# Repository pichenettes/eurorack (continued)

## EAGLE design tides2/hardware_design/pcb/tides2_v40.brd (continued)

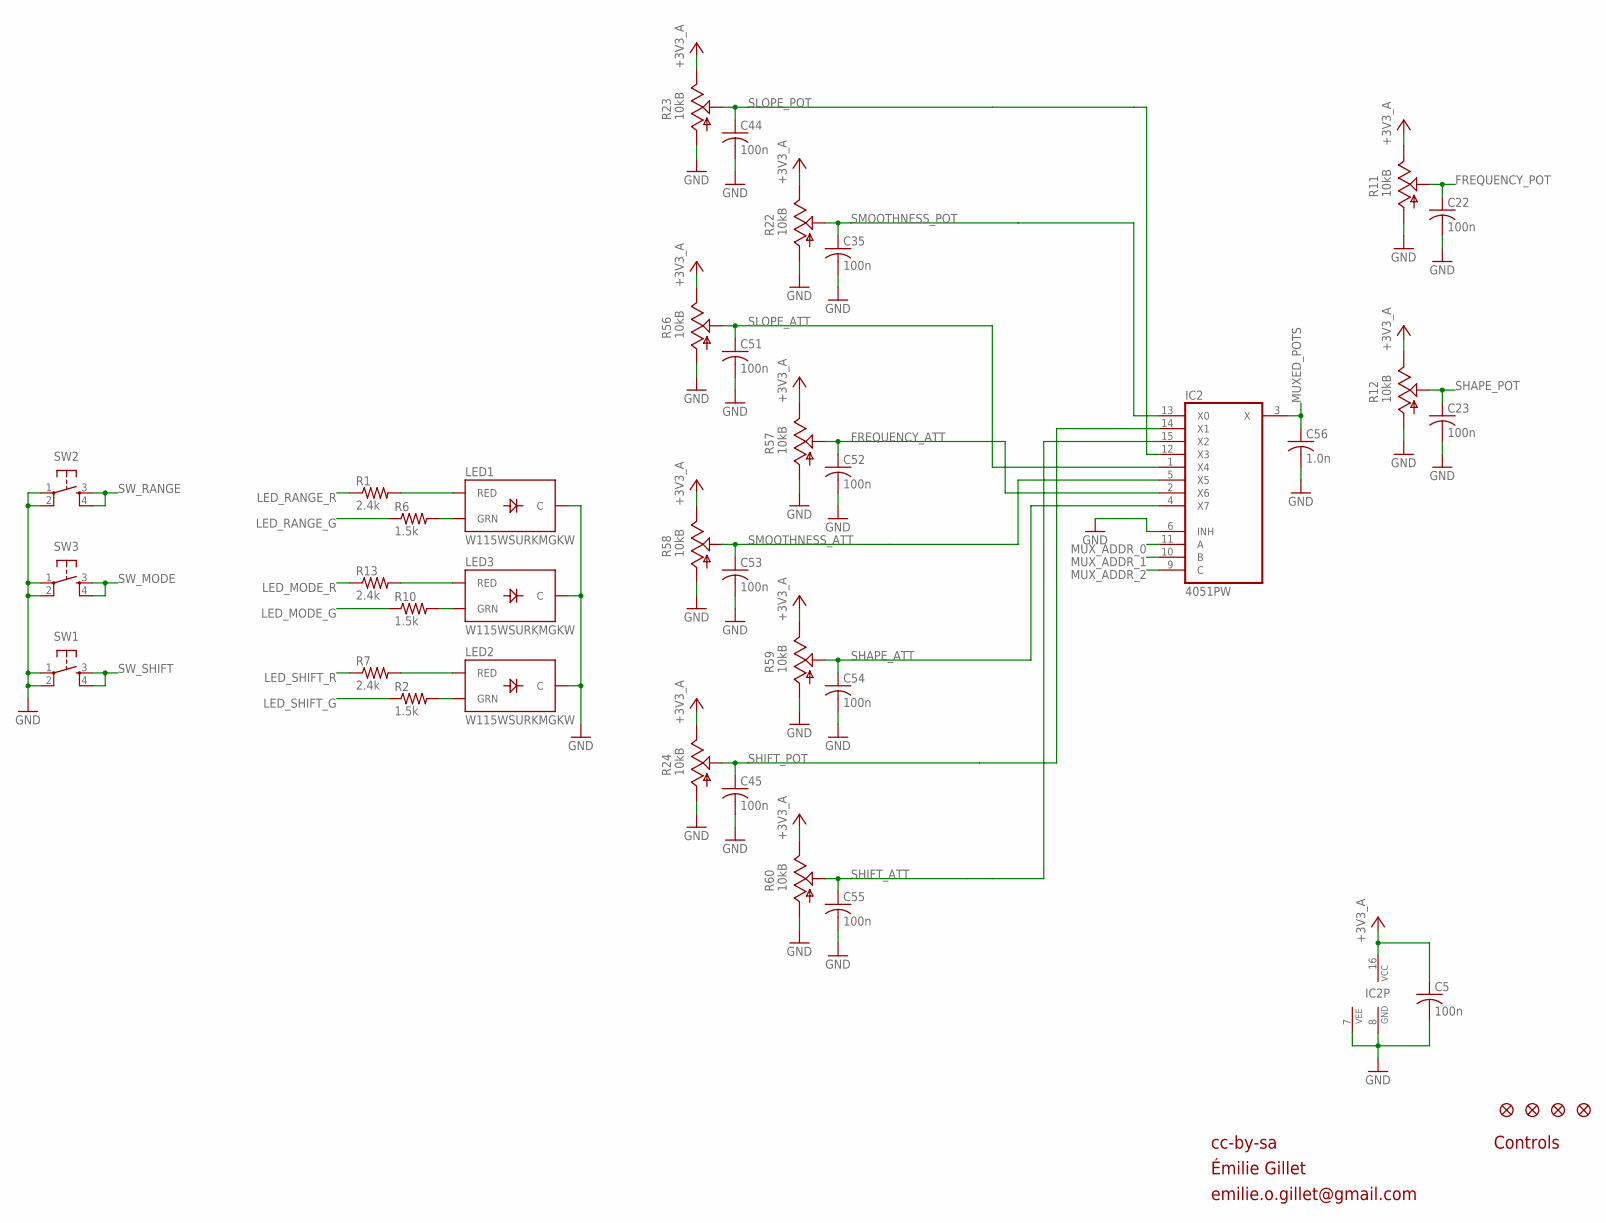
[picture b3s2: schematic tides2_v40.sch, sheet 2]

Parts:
C5, C22, C23, C35, C44, C45, C51, C52, C53, C54, C55: 100n; C0402
C56: 1.0n; C0402
IC2: 4051PW; TSSOP16_065
JP1, JP2, JP3, JP4: FIDUCIAL1X2; FIDUCIAL-1X2
LED1, LED2, LED3: W115WSURKMGKW; LED-BICOLOR-THROUGHHOLE-2.54
R1, R7, R13: 2.4k; R0402
R2, R6, R10: 1.5k; R0402
R11, R12, R22, R23, R24: 10kB; ALPS_POT_VERTICAL_PS
R56, R57, R58, R59, R60: 10kB; ALPS_POT_VERTICAL
SW1, SW2, SW3: TAC_SWITCHPTH; TACTILE-PTH

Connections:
+3V3_A: C5.1, IC2.16 (VCC), R11.P$1 (E), R12.P$1 (E), R22.P$1 (E), R23.P$1 (E), R24.P$1 (E), R56.P$1 (E), R57.P$1 (E), R58.P$1 (E), R59.P$1 (E), R60.P$1 (E); also elsewhere on the board
FREQUENCY_ATT: C52.1, IC2.2 (X6), R57.P$2 (S)
FREQUENCY_POT: C22.1, R11.P$2 (S); also elsewhere on the board
GND: C5.2, C22.2, C23.2, C35.2, C44.2, C45.2, C51.2, C52.2, C53.2, C54.2, C55.2, C56.2, IC2.6 (INH), IC2.7 (VEE), IC2.8 (GND), LED1.2 (C), LED2.2 (C), LED3.2 (C), R11.P$3 (A), R12.P$3 (A), R22.P$3 (A), R23.P$3 (A), R24.P$3 (A), R56.P$3 (A), R57.P$3 (A), R58.P$3 (A), R59.P$3 (A), R60.P$3 (A), SW1.1, SW1.2, SW2.1, SW2.2, SW3.1, SW3.2; also elsewhere on the board
LED_MODE_G: R10.1; also elsewhere on the board
LED_MODE_R: R13.1; also elsewhere on the board
LED_RANGE_G: R6.1; also elsewhere on the board
LED_RANGE_R: R1.1; also elsewhere on the board
LED_SHIFT_G: R2.1; also elsewhere on the board
LED_SHIFT_R: R7.1; also elsewhere on the board
MUXED_POTS: C56.1, IC2.3 (X); also elsewhere on the board
MUX_ADDR_0: IC2.11 (A); also elsewhere on the board
MUX_ADDR_1: IC2.10 (B); also elsewhere on the board
MUX_ADDR_2: IC2.9 (C); also elsewhere on the board
unnamed: LED1.3 (RED), R1.2
unnamed: LED3.3 (RED), R13.2
unnamed: LED3.1 (GRN), R10.2
unnamed: LED2.3 (RED), R7.2
unnamed: LED1.1 (GRN), R6.2
unnamed: LED2.1 (GRN), R2.2
SHAPE_ATT: C54.1, IC2.4 (X7), R59.P$2 (S)
SHAPE_POT: C23.1, R12.P$2 (S); also elsewhere on the board
SHIFT_ATT: C55.1, IC2.15 (X2), R60.P$2 (S)
SHIFT_POT: C45.1, IC2.14 (X1), R24.P$2 (S)
SLOPE_ATT: C51.1, IC2.1 (X4), R56.P$2 (S)
SLOPE_POT: C44.1, IC2.12 (X3), R23.P$2 (S)
SMOOTHNESS_ATT: C53.1, IC2.5 (X5), R58.P$2 (S)
SMOOTHNESS_POT: C35.1, IC2.13 (X0), R22.P$2 (S)
SW_MODE: SW3.3, SW3.4; also elsewhere on the board
SW_RANGE: SW2.3, SW2.4; also elsewhere on the board
SW_SHIFT: SW1.3, SW1.4; also elsewhere on the board

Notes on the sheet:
cc-by-sa
Controls
Émilie Gillet
emilie.o.gillet@gmail.com

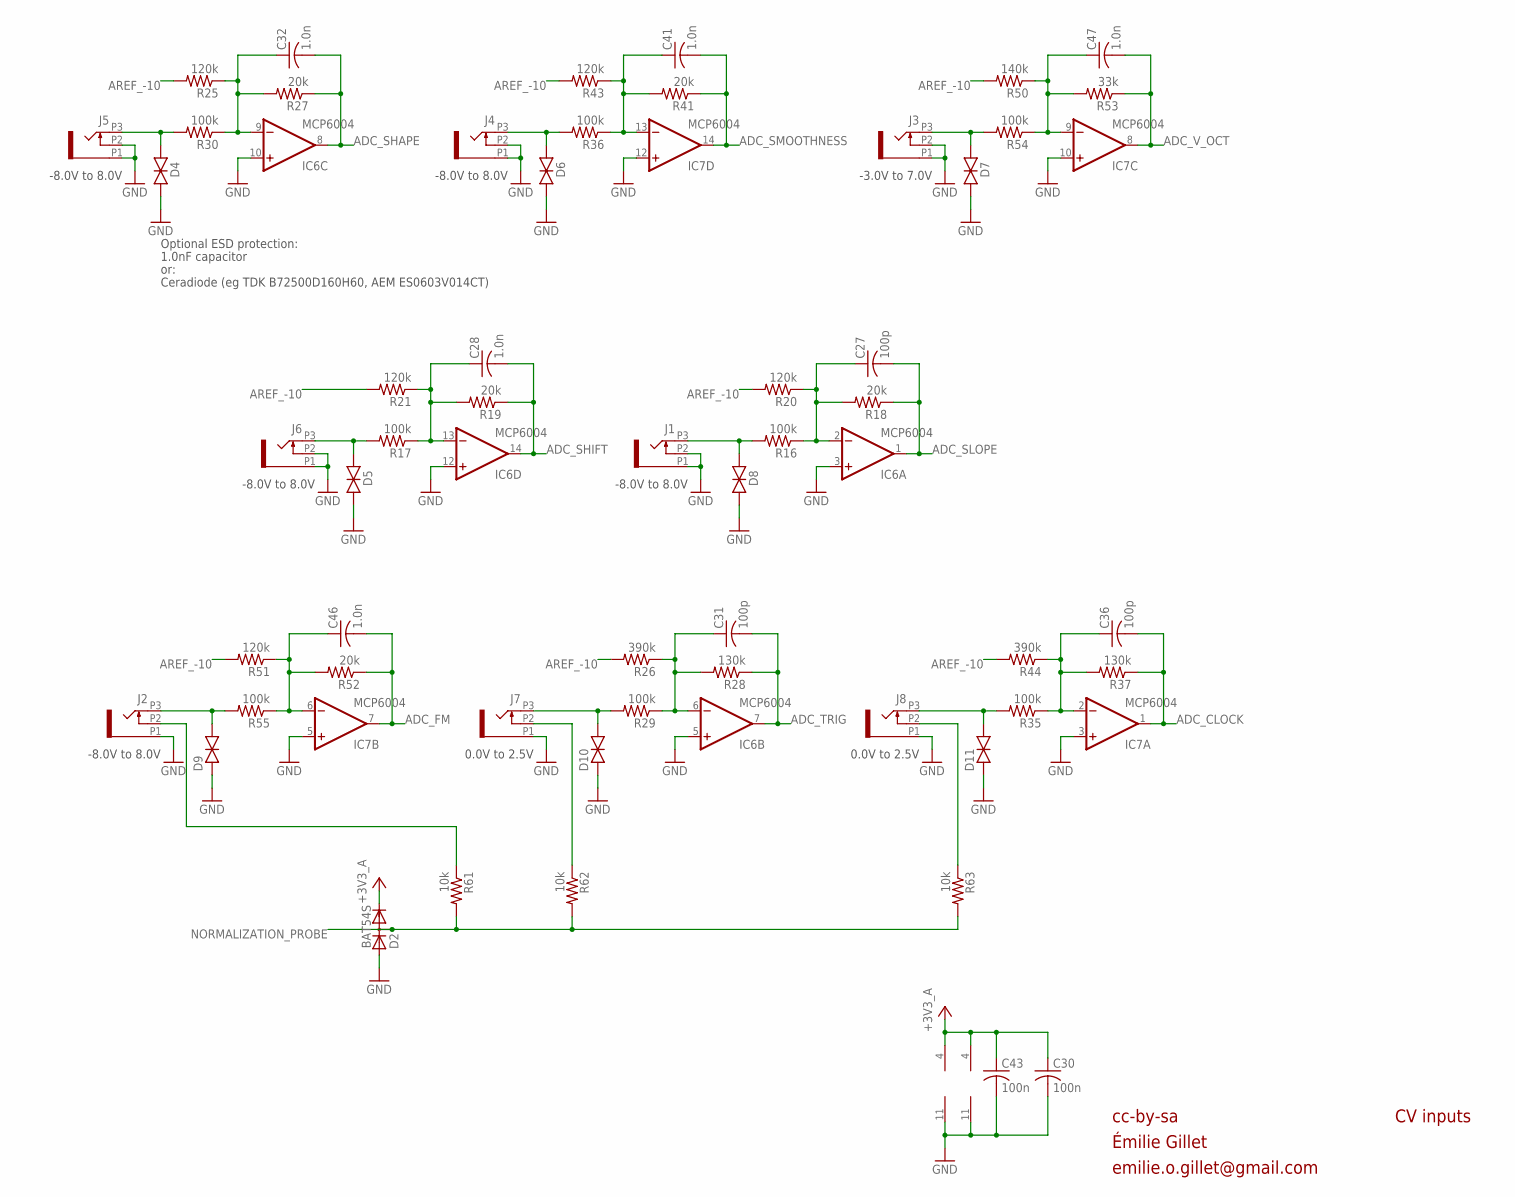
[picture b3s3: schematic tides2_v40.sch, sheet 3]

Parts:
C27, C31, C36: 100p; C0402
C28, C32, C41, C46, C47: 1.0n; C0402
C30, C43: 100n; C0402
D2: BAT54S; SOT23
D4, D5, D6, D7, D8, D9, D10, D11: TVS; 0603
IC6, IC7: MCP6004; TSSOP14_065
J1, J2, J3, J4, J5, J6, J7, J8: PJ301_THONKICONN6; WQP_PJ_301M6
R16, R17, R29, R30, R35, R36, R54, R55: 100k; R0402
R18, R19, R27, R41, R52: 20k; R0402
R20, R21, R25, R43, R51: 120k; R0402
R26, R44: 390k; R0402
R28, R37: 130k; R0402
R50: 140k; R0402
R53: 33k; R0402
R61, R62, R63: 10k; R0402

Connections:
+3V3_A: C30.1, C43.1, D2.2 (C), IC6.4 (V+), IC7.4 (V+); also elsewhere on the board
ADC_CLOCK: C36.2, IC7.1 (OUT), R37.1; also elsewhere on the board
ADC_FM: C46.2, IC7.7 (OUT), R52.1; also elsewhere on the board
ADC_SHAPE: C32.2, IC6.8 (OUT), R27.1; also elsewhere on the board
ADC_SHIFT: C28.2, IC6.14 (OUT), R19.1; also elsewhere on the board
ADC_SLOPE: C27.2, IC6.1 (OUT), R18.1; also elsewhere on the board
ADC_SMOOTHNESS: C41.2, IC7.14 (OUT), R41.1; also elsewhere on the board
ADC_TRIG: C31.2, IC6.7 (OUT), R28.1; also elsewhere on the board
ADC_V_OCT: C47.2, IC7.8 (OUT), R53.1; also elsewhere on the board
AREF_-10: R20.2, R21.2, R25.2, R26.2, R43.2, R44.2, R50.2, R51.2; also elsewhere on the board
CLOCK_IN: D11.2 (C), J8.P3 (3), R35.2
FM_IN: D9.2 (C), J2.P3 (3), R55.2
GND: C30.2, C43.2, D2.1 (A), D4.1 (A), D5.1 (A), D6.1 (A), D7.1 (A), D8.1 (A), D9.1 (A), D10.1 (A), D11.1 (A), IC6.3 (+IN), IC6.5 (+IN), IC6.10 (+IN), IC6.11 (V-), IC6.12 (+IN), IC7.3 (+IN), IC7.5 (+IN), IC7.10 (+IN), IC7.11 (V-), IC7.12 (+IN), J1.P1 (1), J1.P2 (2), J2.P1 (1), J3.P1 (1), J3.P2 (2), J4.P1 (1), J4.P2 (2), J5.P1 (1), J5.P2 (2), J6.P1 (1), J6.P2 (2), J7.P1 (1), J8.P1 (1); also elsewhere on the board
unnamed: J7.P2 (2), R62.1
unnamed: J8.P2 (2), R63.1
unnamed: C27.1, IC6.2 (-IN), R16.1, R18.2, R20.1
unnamed: J2.P2 (2), R61.1
unnamed: C28.1, IC6.13 (-IN), R17.1, R19.2, R21.1
unnamed: C47.1, IC7.9 (-IN), R50.1, R53.2, R54.1
unnamed: C46.1, IC7.6 (-IN), R51.1, R52.2, R55.1
unnamed: C31.1, IC6.6 (-IN), R26.1, R28.2, R29.1
unnamed: C32.1, IC6.9 (-IN), R25.1, R27.2, R30.1
unnamed: C36.1, IC7.2 (-IN), R35.1, R37.2, R44.1
unnamed: C41.1, IC7.13 (-IN), R36.1, R41.2, R43.1
NORMALIZATION_PROBE: D2.3 (AC), R61.2, R62.2, R63.2; also elsewhere on the board
SHAPE_IN: D4.2 (C), J5.P3 (3), R30.2
SHIFT_IN: D5.2 (C), J6.P3 (3), R17.2
SLOPE_IN: D8.2 (C), J1.P3 (3), R16.2
SMOOTHNESS_IN: D6.2 (C), J4.P3 (3), R36.2
TRIG_IN: D10.2 (C), J7.P3 (3), R29.2
V_OCT_IN: D7.2 (C), J3.P3 (3), R54.2

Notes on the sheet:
cc-by-sa
CV inputs
-8.0V to 8.0V
-3.0V to 7.0V
0.0V to 2.5V
Optional ESD protection:
1.0nF capacitor
or:
Ceradiode (eg TDK B72500D160H60, AEM ES0603V014CT)
Émilie Gillet
emilie.o.gillet@gmail.com

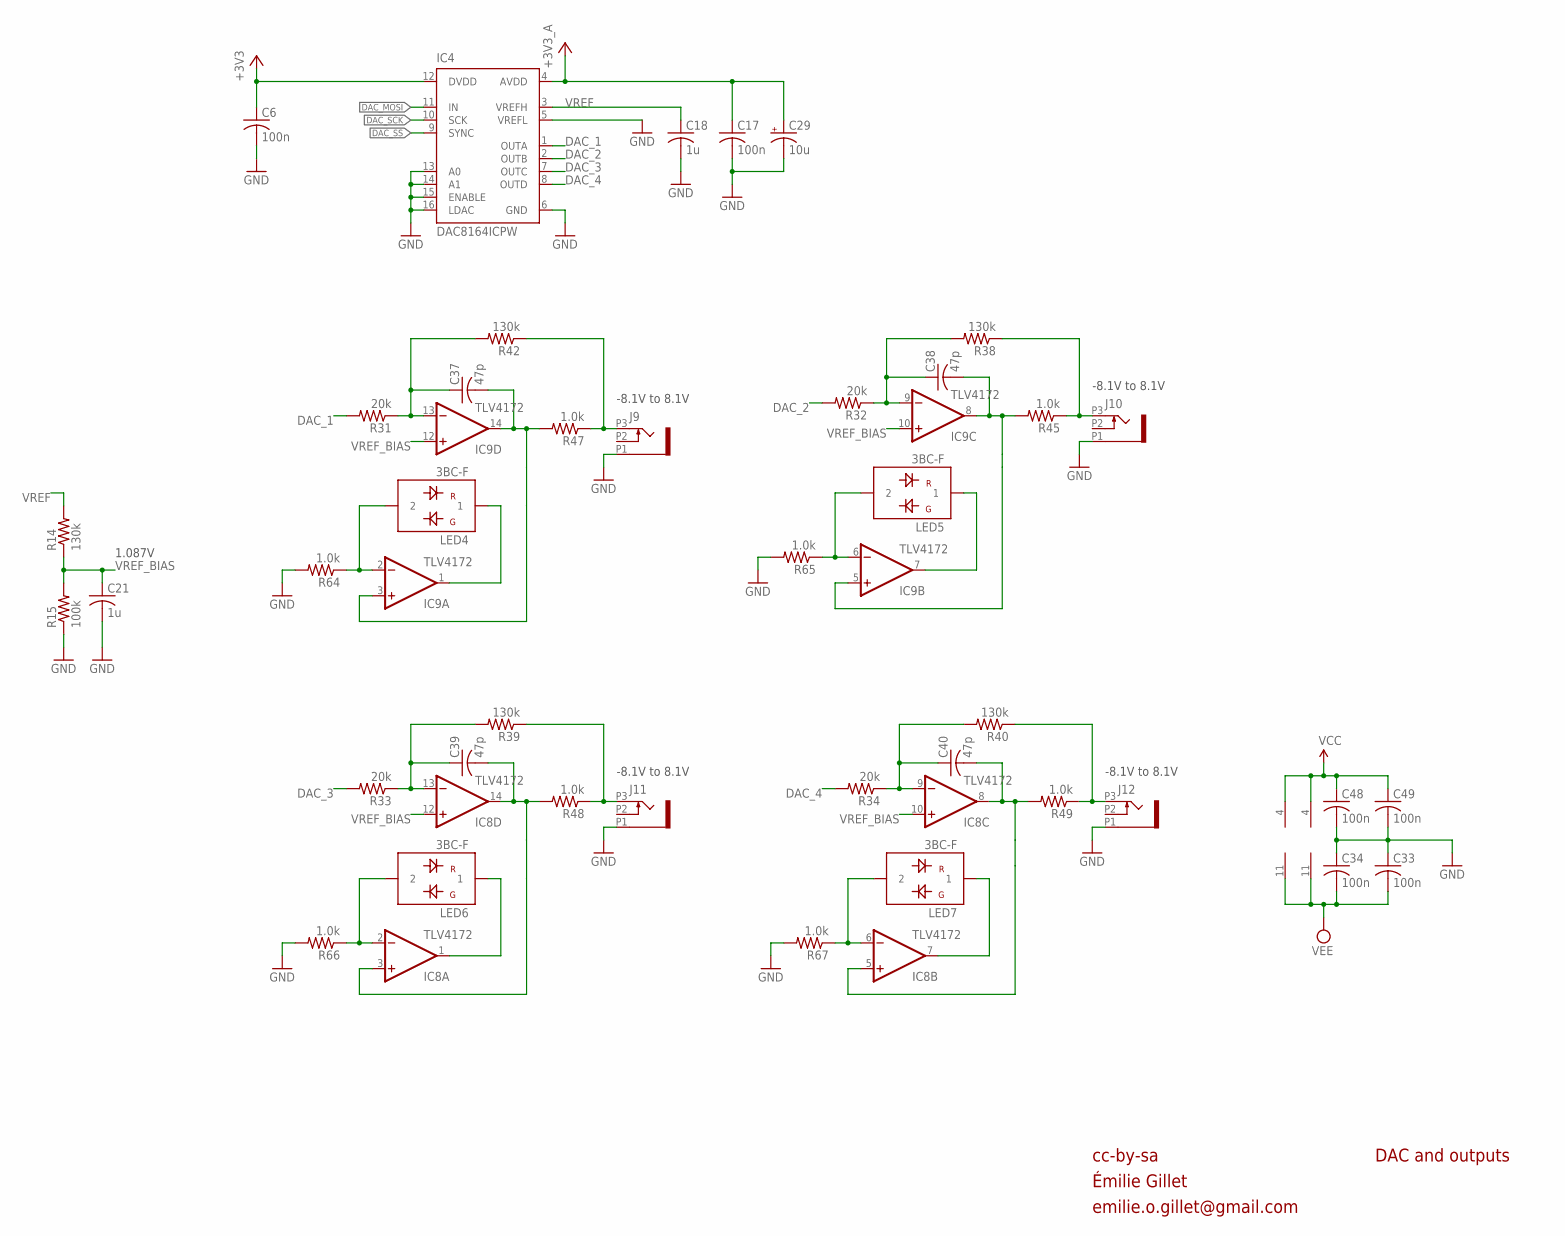
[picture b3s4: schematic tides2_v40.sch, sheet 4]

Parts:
C6, C17, C33, C34, C48, C49: 100n; C0402
C18, C21: 1u; C0402
C29: 10u; PANASONIC_A
C37, C38, C39, C40: 47p; C0402
IC4: DAC8164ICPW; SOP65P640X110-16N
IC8, IC9: TLV4172; TSSOP14_065
J9, J10, J11, J12: PJ301_THONKICONN6; WQP_PJ_301M6
LED4, LED5, LED6, LED7: 3BC-F; LED3MM
R14, R38, R39, R40, R42: 130k; R0402
R15: 100k; R0402
R31, R32, R33, R34: 20k; R0402
R45, R47, R48, R49: 1.0k; R0603
R64, R65, R66, R67: 1.0k; R0402

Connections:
+3V3: C6.1, IC4.12 (DVDD); also elsewhere on the board
+3V3_A: C17.1, C29.+, IC4.4 (AVDD); also elsewhere on the board
DAC_1: IC4.1 (OUTA), R31.2
DAC_2: IC4.2 (OUTB), R32.2
DAC_3: IC4.7 (OUTC), R33.2
DAC_4: IC4.8 (OUTD), R34.2
DAC_MOSI: IC4.11 (IN); also elsewhere on the board
DAC_SCK: IC4.10 (SCK); also elsewhere on the board
DAC_SS: IC4.9 (SYNC); also elsewhere on the board
GND: C6.2, C17.2, C18.2, C21.2, C29.-, C33.1, C34.1, C48.2, C49.2, IC4.5 (VREFL), IC4.6 (GND), IC4.13 (A0), IC4.14 (A1), IC4.15 (ENABLE), IC4.16 (LDAC), J9.P1 (1), J10.P1 (1), J11.P1 (1), J12.P1 (1), R15.1, R64.2, R65.2, R66.2, R67.2; also elsewhere on the board
unnamed: C37.2, IC9.3 (+IN), IC9.14 (OUT), R47.2
unnamed: J11.P3 (3), R39.1, R48.1
unnamed: J9.P3 (3), R42.1, R47.1
unnamed: C39.1, IC8.13 (-IN), R33.1, R39.2
unnamed: J12.P3 (3), R40.1, R49.1
unnamed: C40.1, IC8.9 (-IN), R34.1, R40.2
unnamed: C38.1, IC9.9 (-IN), R32.1, R38.2
unnamed: C37.1, IC9.13 (-IN), R31.1, R42.2
unnamed: J10.P3 (3), R38.1, R45.1
unnamed: IC9.2 (-IN), LED4.2, R64.1
unnamed: IC9.1 (OUT), LED4.1
unnamed: C38.2, IC9.5 (+IN), IC9.8 (OUT), R45.2
unnamed: IC9.6 (-IN), LED5.2, R65.1
unnamed: IC9.7 (OUT), LED5.1
unnamed: C39.2, IC8.3 (+IN), IC8.14 (OUT), R48.2
unnamed: IC8.2 (-IN), LED6.2, R66.1
unnamed: IC8.1 (OUT), LED6.1
unnamed: C40.2, IC8.5 (+IN), IC8.8 (OUT), R49.2
unnamed: IC8.6 (-IN), LED7.2, R67.1
unnamed: IC8.7 (OUT), LED7.1
VCC: C48.1, C49.1, IC8.4 (V+), IC9.4 (V+); also elsewhere on the board
VEE: C33.2, C34.2, IC8.11 (V-), IC9.11 (V-); also elsewhere on the board
VREF: C18.1, IC4.3 (VREFH), R14.2
VREF_BIAS: C21.1, IC8.10 (+IN), IC8.12 (+IN), IC9.10 (+IN), IC9.12 (+IN), R14.1, R15.2

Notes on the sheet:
cc-by-sa
DAC and outputs
-8.1V to 8.1V
1.087V
Émilie Gillet
emilie.o.gillet@gmail.com

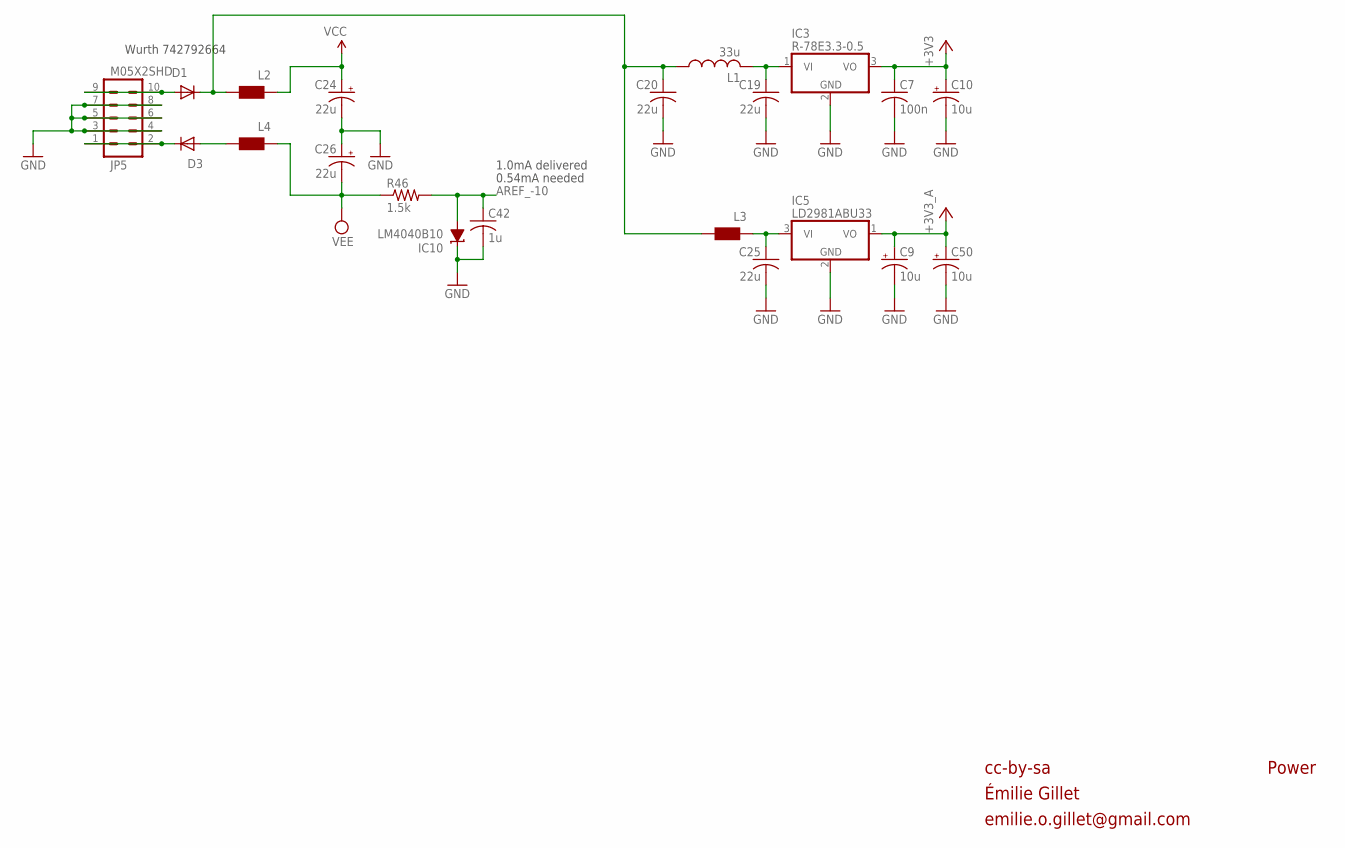
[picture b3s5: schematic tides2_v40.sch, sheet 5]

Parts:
C7: 100n; C0402
C9, C10, C50: 10u; PANASONIC_A
C19, C20, C25: 22u; C1206
C24, C26: 22u; PANASONIC_B
C42: 1u; C0402
D1, D3: 1N5819HW; SOD123
IC3: R-78E3.3-0.5; WE78
IC5: LD2981ABU33; SOT89
IC10: LM4040B10; DBZ_R-PDSO-G3
JP5: M05X2SHD; 2X5-SHROUDED
L1: 33u; L2012C
L2, L3, L4: WE-CBF_0603; 0603
R46: 1.5k; R0402

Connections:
+3V3: C7.1, C10.+, IC3.3 (VO); also elsewhere on the board
+3V3_A: C9.+, C50.+, IC5.1 (VO); also elsewhere on the board
AREF_-10: C42.1, IC10.2 (A), R46.2; also elsewhere on the board
GND: C7.2, C9.-, C10.-, C19.2, C20.2, C24.-, C25.2, C26.+, C42.2, C50.-, IC3.2 (GND), IC5.2 (GND), IC10.1 (C), JP5.3, JP5.4, JP5.5, JP5.6, JP5.7, JP5.8; also elsewhere on the board
unnamed: C19.1, IC3.1 (VI), L1.2
unnamed: D3.A, L4.2
unnamed: C20.1, D1.C, L1.1, L2.2, L3.2
unnamed: C25.1, IC5.3 (VI), L3.1
unnamed: D1.A, JP5.9, JP5.10
unnamed: D3.C, JP5.1, JP5.2
VCC: C24.+, L2.1; also elsewhere on the board
VEE: C26.-, L4.1, R46.1; also elsewhere on the board

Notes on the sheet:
cc-by-sa
Power
0.54mA needed
Wurth 742792664
1.0mA delivered
Émilie Gillet
emilie.o.gillet@gmail.com

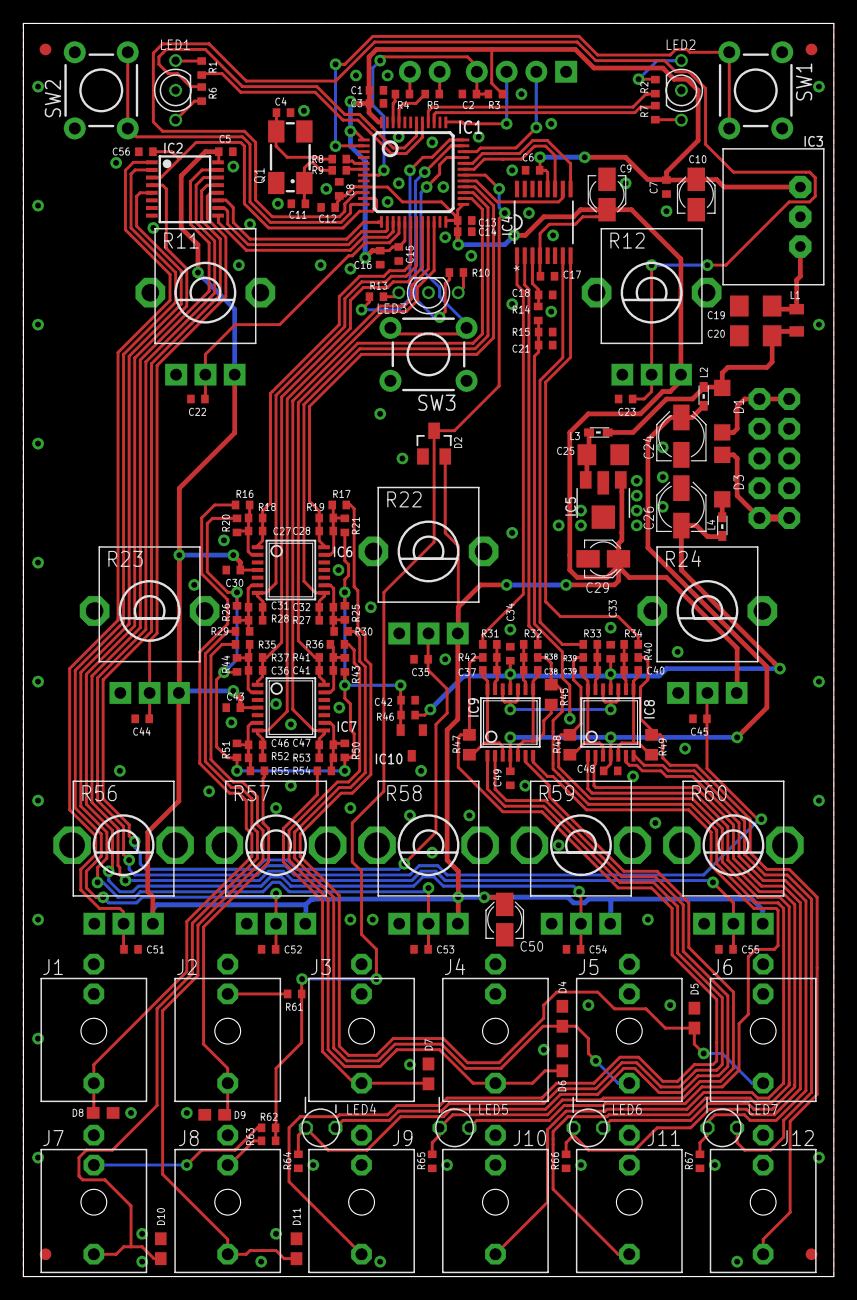
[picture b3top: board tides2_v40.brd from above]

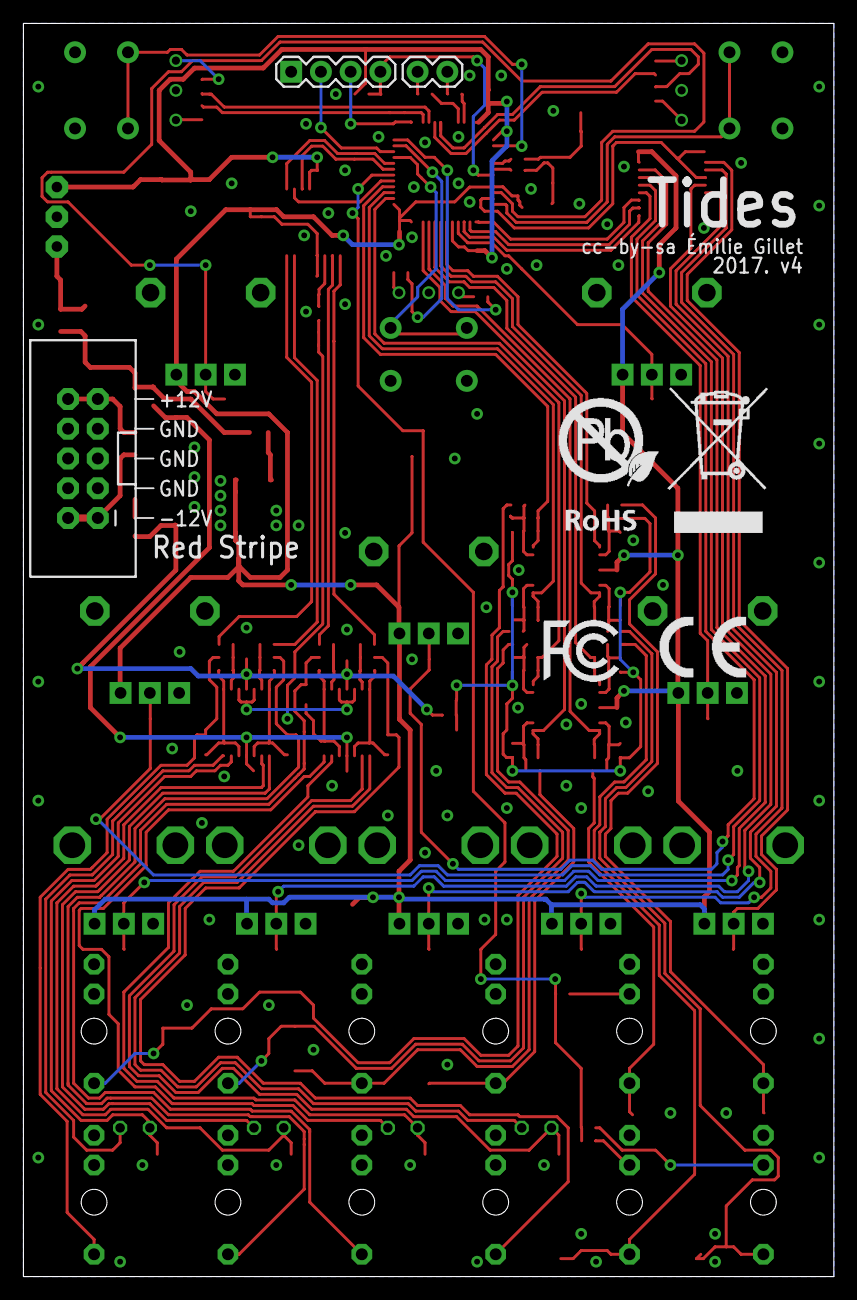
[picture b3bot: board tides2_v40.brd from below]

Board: 2 copper layers, 69.2 x 107.0 mm, 181 parts (6 on the bottom side), 109 nets.

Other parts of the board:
U$2: ROHS_BIG
U$4: CE_MEDIUM
U$5: FCC_MEDIUM

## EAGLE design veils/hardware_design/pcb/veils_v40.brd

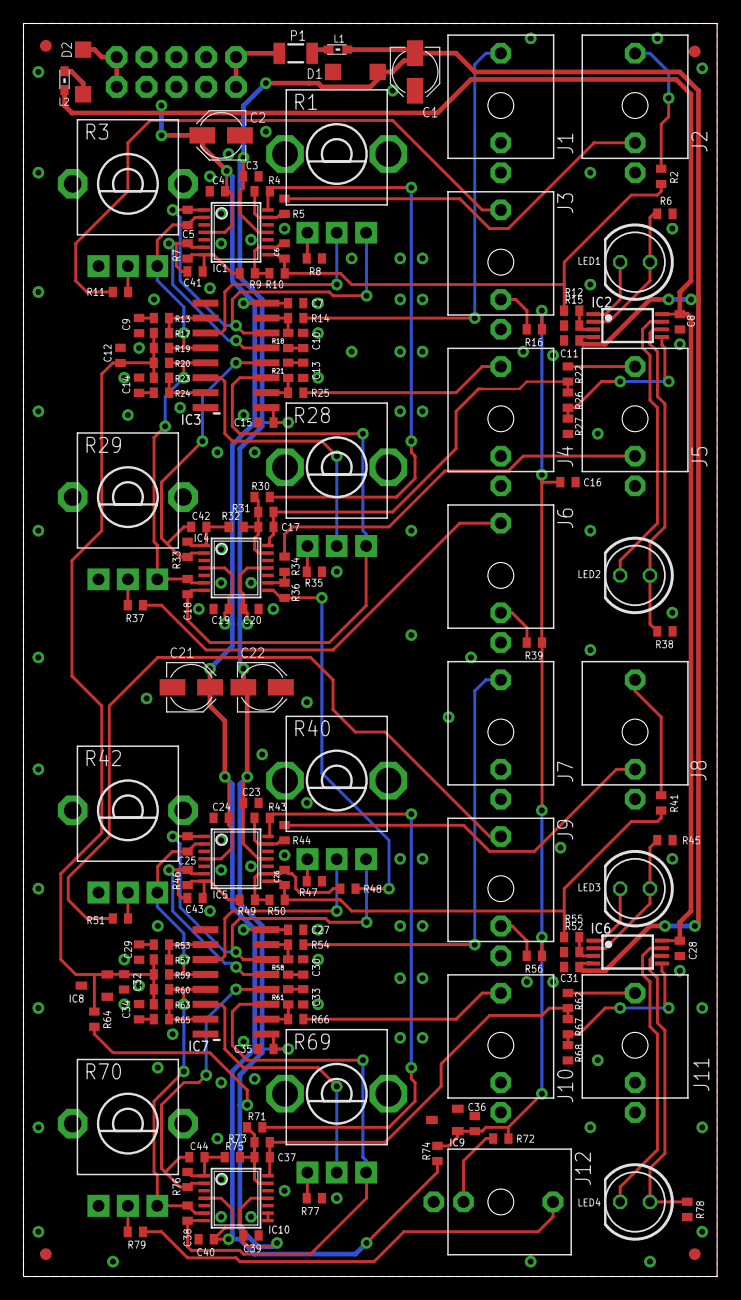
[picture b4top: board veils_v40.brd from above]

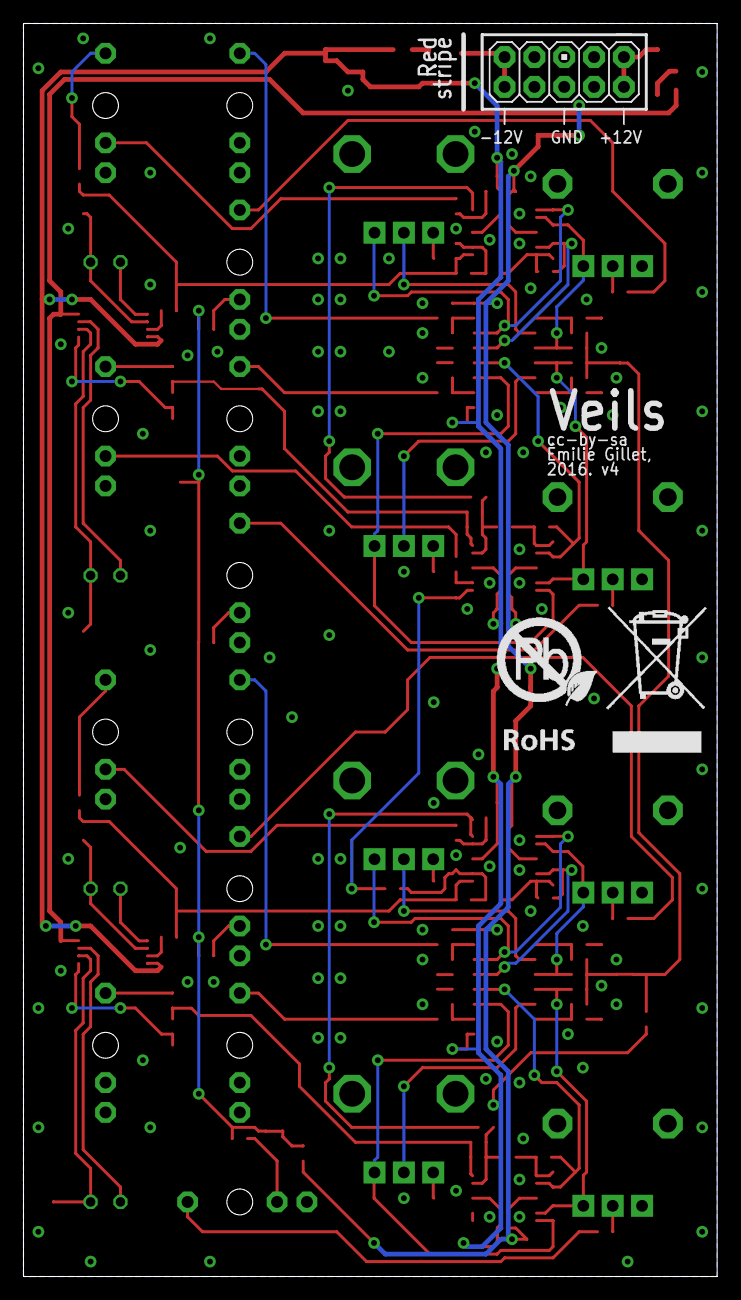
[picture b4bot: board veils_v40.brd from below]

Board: 2 copper layers, 59.1 x 106.7 mm, 160 parts (2 on the bottom side), 99 nets.

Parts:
C1, C2, C21, C22: 22u; PANASONIC_B
C3, C4, C7, C8, C11, C15, C19, C20, C23, C24, C27, C28, C31, C35, C39, C40: 100n; C0402
C5, C18, C25, C38, C41, C42, C43, C44: 47p; C0402
C6, C17, C26, C37: 100p; C0402
C9, C10, C13, C14, C29, C30, C33, C34: 560p; C0402
C12, C16, C32, C36: 470n; C0402
D1, D2: 1N5819HW; SOD123
IC1, IC4, IC5, IC10: OPA1654; TSSOP14
IC2, IC6: LM358PW; TSSOP8
IC3, IC7: V2164SZ; SOIC16N
IC8: LM4040C25; DBZ_R-PDSO-G3
IC9: LM4040C10; DBZ_R-PDSO-G3
J1, J2, J3, J4, J5, J6, J7, J8, J9, J10, J11, J12: PJ301_THONKICONN6; WQP_PJ_301M6
JP1, JP2, JP3, JP4: FIDUCIAL1X2; FIDUCIAL-1X2
JP5: M05X2PTH; AVR_ICSP
L1, L2: 742792664; 0603
LED1, LED2, LED3, LED4: WP7113SRSGW; LED5MM
P1: PTCSMD; PTC-1206
R1, R28, R40, R69: 10kB; ALPS_POT_VERTICAL
R2, R8, R13, R18, R21, R22, R24, R35, R41, R47, R53, R58, R61, R62, R65, R77: 510; R0402
R3, R29, R42, R70: 10kB; ALPS_POT_VERTICAL_PS
R4, R36, R43: 5.6k; R0402
R5, R9, R10, R30, R31, R32, R34, R44, R48, R49, R50, R71, R73, R75: 5.1k; R0402
R6, R38, R45, R78: 1.2k; R0402
R7, R11, R14, R25, R33, R37, R46, R51, R54, R66, R76, R79: 100k; R0402
R12, R15, R26, R27, R52, R55, R67, R68: 1.0M; R0402
R16, R39, R56, R64, R72: 24k; R0402
R17, R23, R57, R63: 49.9k; R0402
R19, R20, R59, R60: 20M; R0402
R74: 3.6k; R0402
U$2: ROHS_BIG

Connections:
1_TO_2: IC1.14, R4.1, R30.2
2_TO_3: IC4.8, R36.1, R48.2
3_TO_4: IC5.14, R43.1, R71.2
AREF_+10: C16.1, C36.1, IC9.1, R16.2, R39.2, R56.2, R72.2, R74.2
AREF_-2.5: C12.1, C32.1, IC8.2, R17.2, R19.2, R20.2, R23.2, R57.2, R59.2, R60.2, R63.2, R64.2
CV_IN_1: J3.P3, R11.2
FOO: IC3.2, R13.2, R17.1
FOO1: IC3.7, R23.1, R24.2
FOO2: IC7.2, R53.2, R57.1
FOO3: IC7.7, R63.1, R65.2
GND: C1.+, C2.-, C3.1, C4.2, C7.2, C8.2, C9.2, C10.2, C11.1, C12.2, C13.2, C14.2, C15.1, C16.2, C19.2, C20.1, C21.-, C22.+, C23.1, C24.2, C27.2, C28.2, C29.2, C30.2, C31.1, C32.2, C33.2, C34.2, C35.1, C36.2, C39.1, C40.2, D1.C, IC1.3, IC1.5, IC1.10, IC1.12, IC3.8, IC4.3, IC4.5, IC4.10, IC4.12, IC5.3, IC5.5, IC5.10, IC5.12, IC7.8, IC8.1, IC9.2, IC10.3, IC10.5, IC10.10, IC10.12, J1.P1, J1.P2, J2.P1, J3.P1, J4.P1, J4.P2, J5.P1, J6.P1, J7.P1, J7.P2, J8.P1, J9.P1, J10.P1, J10.P2, J11.P1, J12.P1, JP5.3, JP5.4, JP5.5, JP5.6, JP5.7, JP5.8, R3.P$3, R6.2, R8.1, R15.1, R27.1, R29.P$3, R35.1, R38.2, R42.P$3, R45.2, R47.1, R55.1, R68.1, R70.P$3, R77.1, R78.2
unnamed: IC2.3, R12.2, R15.2
unnamed: IC10.8, IC10.9
unnamed: J4.P3, R25.2
unnamed: IC2.5, R26.2, R27.2
unnamed: IC6.3, R52.2, R55.2
unnamed: J5.P3, R22.1
unnamed: J2.P3, R2.1
unnamed: IC6.5, R67.2, R68.2
unnamed: IC3.3, R1.P$2
unnamed: C6.1, IC1.9, R9.1, R10.2
unnamed: D2.A, JP5.1, JP5.2
unnamed: JP5.9, JP5.10, P1.2
unnamed: L1.2, P1.1
unnamed: R3.P$2, R11.1
unnamed: R1.P$3, R8.2
unnamed: D2.C, L2.2
unnamed: C13.1, R21.1
unnamed: IC2.1, LED1.K
unnamed: IC2.2, LED1.A, R6.1
unnamed: C9.1, R13.1
unnamed: J3.P2, R16.1
unnamed: IC1.13, R4.2, R5.1
unnamed: J8.P3, R41.1
unnamed: IC3.10, R21.2, R25.1
unnamed: J2.P2, R5.2
unnamed: IC3.6, R28.P$2
unnamed: C17.1, IC4.13, R30.1, R31.2, R32.1
unnamed: C18.2, IC3.11, IC4.7, R28.P$1
unnamed: IC7.3, R40.P$2
unnamed: C25.2, IC5.1, IC7.14, R40.P$1
unnamed: R28.P$3, R35.2
unnamed: C38.2, IC7.11, IC10.7, R69.P$1
unnamed: R40.P$3, R47.2
unnamed: IC2.7, LED2.K
unnamed: IC2.6, LED2.A, R38.1
unnamed: IC4.9, R34.1, R36.2
unnamed: J5.P2, R34.2
unnamed: C42.2, IC4.1, R32.2, R33.1
unnamed: R29.P$2, R37.1
unnamed: C14.1, R24.1
unnamed: C18.1, IC3.5, IC4.6, R20.1, R29.P$1
unnamed: IC7.6, R69.P$2
unnamed: J6.P3, R37.2
unnamed: C30.1, R58.1
unnamed: IC7.15, R54.1, R58.2
unnamed: C10.1, R18.1
unnamed: C26.1, IC5.9, R48.1, R49.1, R50.2
unnamed: J9.P2, R56.1
unnamed: R69.P$3, R77.2
unnamed: J7.P3, R54.2
unnamed: C42.1, IC3.12, IC4.2, R33.2
unnamed: J9.P3, R51.2
unnamed: C43.1, IC5.6, IC7.13, R46.2
unnamed: IC6.1, LED3.K
unnamed: IC6.2, LED3.A, R45.1
unnamed: IC5.13, R43.2, R44.1
unnamed: J8.P2, R44.2
unnamed: C44.1, IC7.12, IC10.2, R76.2
unnamed: C29.1, R53.1
unnamed: J6.P2, R39.1
unnamed: C5.1, IC1.2, IC3.4, R3.P$1, R19.1
unnamed: J1.P3, R14.2
unnamed: C25.1, IC5.2, IC7.4, R42.P$1, R59.1
unnamed: J10.P3, R66.2
unnamed: R42.P$2, R51.1
unnamed: J11.P3, R62.1
unnamed: C33.1, R61.1
unnamed: IC7.10, R61.2, R66.1
unnamed: IC3.15, R14.1, R18.2
unnamed: C37.1, IC10.13, R71.1, R73.2, R75.1
unnamed: J12.P3, R79.2
unnamed: IC6.7, LED4.K
unnamed: IC6.6, LED4.A, R78.1
unnamed: C5.2, IC1.1, IC3.14, R1.P$1
unnamed: C44.2, IC10.1, R75.2, R76.1
unnamed: R70.P$2, R79.1
unnamed: C34.1, R65.1
unnamed: C38.1, IC7.5, IC10.6, R60.1, R70.P$1
unnamed: C41.1, IC1.6, IC3.13, R7.2
unnamed: C41.2, IC1.7, R7.1, R9.2
unnamed: C43.2, IC5.7, R46.1, R49.2
unnamed: J12.P2, R72.1
OUT1: C6.2, IC1.8, R2.2, R10.1, R12.1
OUT2: C17.2, IC4.14, R22.2, R26.1, R31.1
OUT3: C26.2, IC5.8, R41.2, R50.1, R52.1
OUT4: C37.2, IC10.14, R62.2, R67.1, R73.1
VCC: C2.+, C4.1, C7.1, C8.1, C19.1, C21.+, C24.1, C27.1, C28.1, C40.1, IC1.4, IC2.8, IC3.16, IC4.4, IC5.4, IC6.8, IC7.16, IC10.4, L2.1, R74.1
VEE: C1.-, C3.2, C11.2, C15.2, C20.2, C22.-, C23.2, C31.2, C35.2, C39.2, D1.A, IC1.11, IC2.4, IC3.9, IC4.11, IC5.11, IC6.4, IC7.9, IC10.11, L1.1, R64.1
